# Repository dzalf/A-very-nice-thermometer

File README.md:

# A-very-nice-thermometer
A decorative thermometer based on the LM95071

Result from my first explorations with KiCAD 5 back in 2018 (?). Recently upgraded to KiCAD 7.0 and ported to Cadlab.io

Tons of corrections are still pending, however, the original design remains intact.

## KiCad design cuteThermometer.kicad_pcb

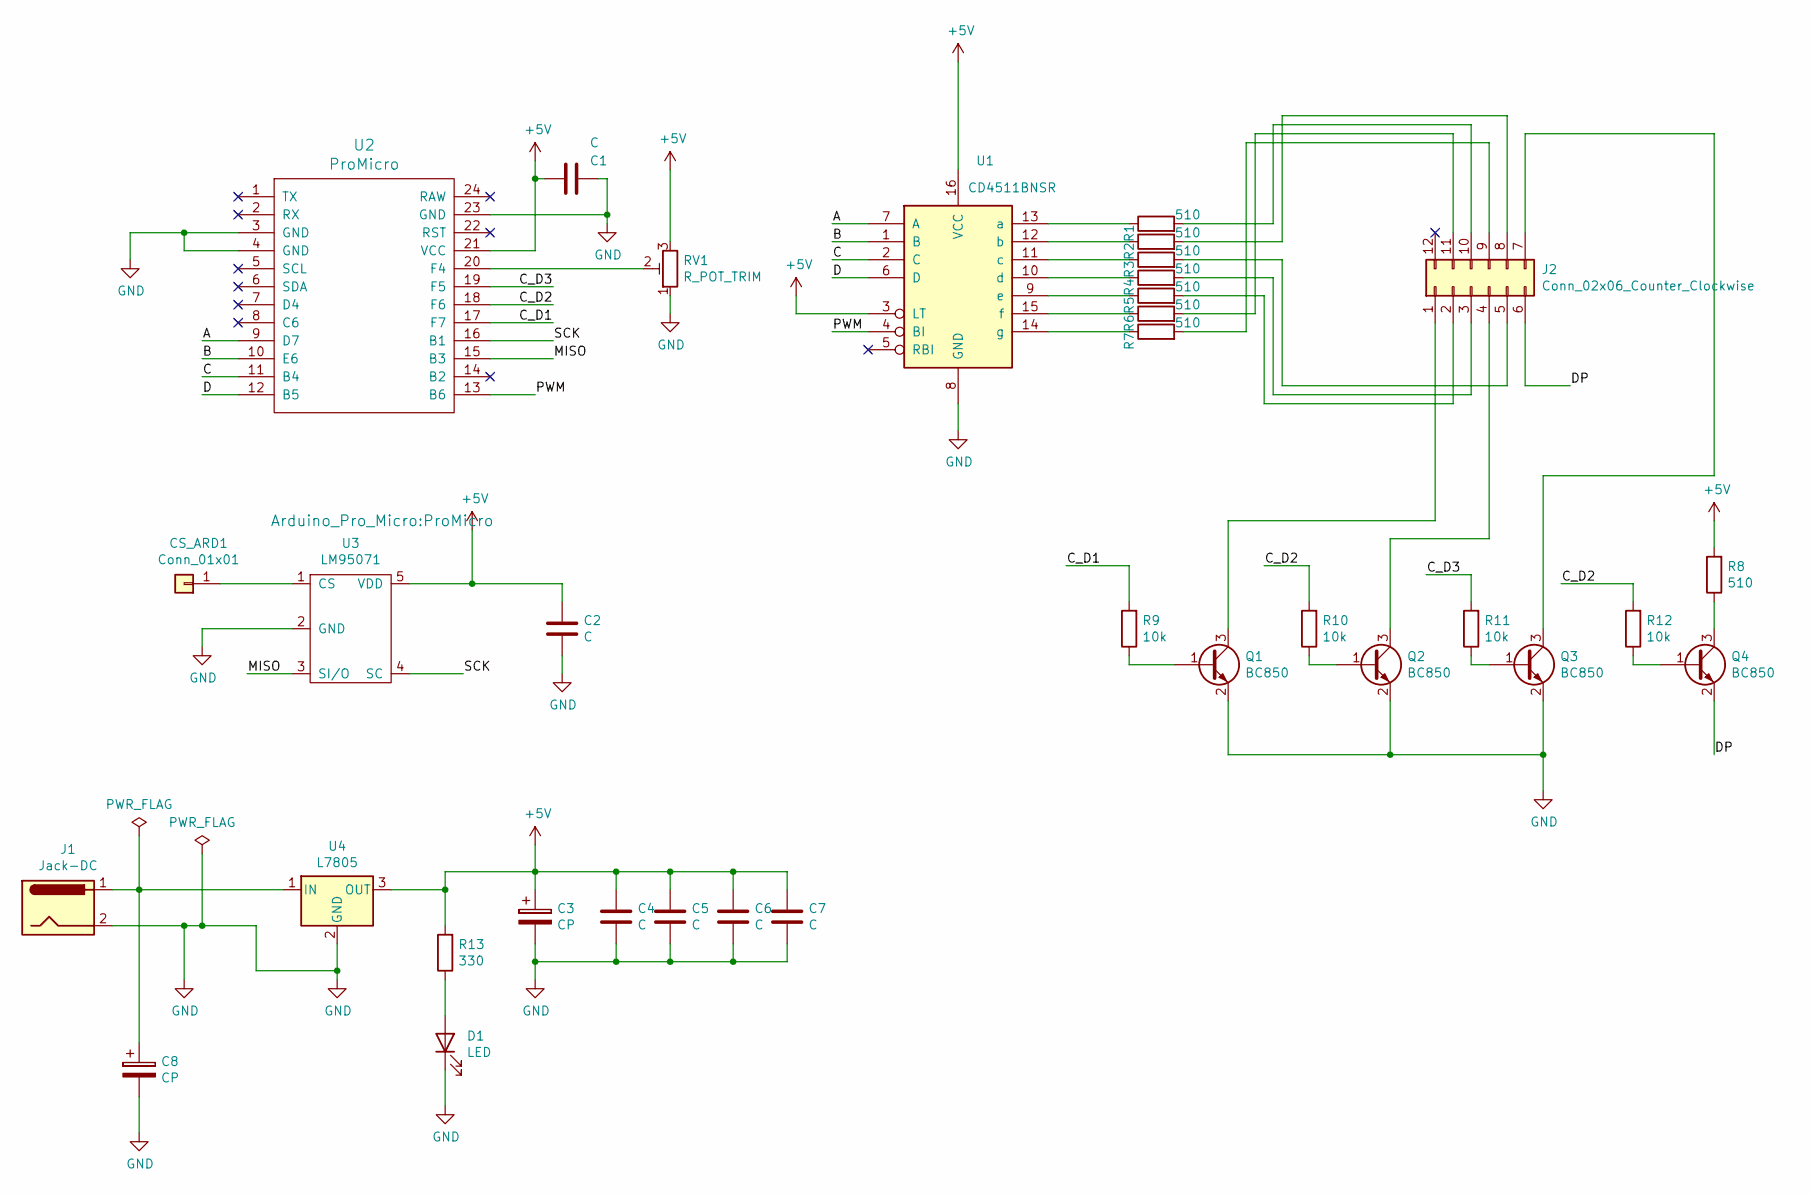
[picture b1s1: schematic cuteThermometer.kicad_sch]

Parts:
C1, C2, C4, C5, C6, C7: C; C_0805_2012Metric_Pad1.15x1.40mm_HandSolder
C3, C8: CP; CP_Elec_4x5.4
CS_ARD1: Conn_01x01; PinHeader_1x01_P1.00mm_Vertical
D1: LED; LED_1206_3216Metric_Pad1.42x1.75mm_HandSolder
J1: Jack-DC; BarrelJack_Wuerth_6941xx301002
J2: Conn_02x06_Counter_Clockwise; PinHeader_2x06_P2.54mm_Vertical
Q1, Q2, Q3, Q4: BC850; SOT-23
R1, R2, R3, R4, R5, R6, R7, R8: 510; R_0805_2012Metric_Pad1.15x1.40mm_HandSolder
R9, R10, R11, R12: 10k; R_0805_2012Metric_Pad1.15x1.40mm_HandSolder
R13: 330; R_0805_2012Metric_Pad1.15x1.40mm_HandSolder
RV1: R_POT_TRIM; Potentiometer_Trimmer-EVM3E
U1: CD4511BNSR; SOP-16_4.4x10.4mm_P1.27mm
U2: ProMicro
U3: LM95071; SOT-23-5_HandSoldering
U4: L7805; TO-252-3_TabPin2

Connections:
+5V: C1.2, C2.1, C3.1, C4.1, C5.1, C6.1, C7.1, R8.2, R13.2, RV1.3, U1.3 (LT), U1.16 (VCC), U2.21 (VCC), U3.5 (VDD), U4.3 (OUT)
/A: U1.7 (A), U2.9 (D7)
/B: U1.1 (B), U2.10 (E6)
/C: U1.2 (C), U2.11 (B4)
/C_D1: R9.2, U2.17 (F7)
/C_D2: R10.2, R12.2, U2.18 (F6)
/C_D3: R11.2, U2.19 (F5)
/D: U1.6 (D), U2.12 (B5)
/DP: J2.6, Q4.2 (E)
/MISO: U2.15 (B3), U3.3 (SI/O)
/PWM: U1.4 (BI), U2.13 (B6)
/SCK: U2.16 (B1), U3.4 (SC)
GND: C1.1, C2.2, C3.2, C4.2, C5.2, C6.2, C7.2, C8.2, D1.1 (K), J1.2, Q1.2 (E), Q2.2 (E), Q3.2 (E), RV1.1, U1.8 (GND), U2.3 (GND), U2.4 (GND), U2.23 (GND), U3.2 (GND), U4.2 (GND)
unnamed: C8.1, J1.1, U4.1 (IN)
unnamed: CS_ARD1.1, U3.1 (CS)
unnamed: D1.2 (A), R13.1
unnamed: J2.1, Q1.3 (C)
unnamed: J2.2, R5.2
unnamed: J2.3, R4.2
unnamed: J2.4, Q2.3 (C)
unnamed: J2.5, R3.2
unnamed: J2.7, Q3.3 (C)
unnamed: J2.8, R2.2
unnamed: J2.9, R7.2
unnamed: J2.10, R1.2
unnamed: J2.11, R6.2
unnamed: Q1.1 (B), R9.1
unnamed: Q2.1 (B), R10.1
unnamed: Q3.1 (B), R11.1
unnamed: Q4.1 (B), R12.1
unnamed: Q4.3 (C), R8.1
unnamed: R1.1, U1.13 (a)
unnamed: R2.1, U1.12 (b)
unnamed: R3.1, U1.11 (c)
unnamed: R4.1, U1.10 (d)
unnamed: R5.1, U1.9 (e)
unnamed: R6.1, U1.15 (f)
unnamed: R7.1, U1.14 (g)
unnamed: RV1.2, U2.20 (F4)

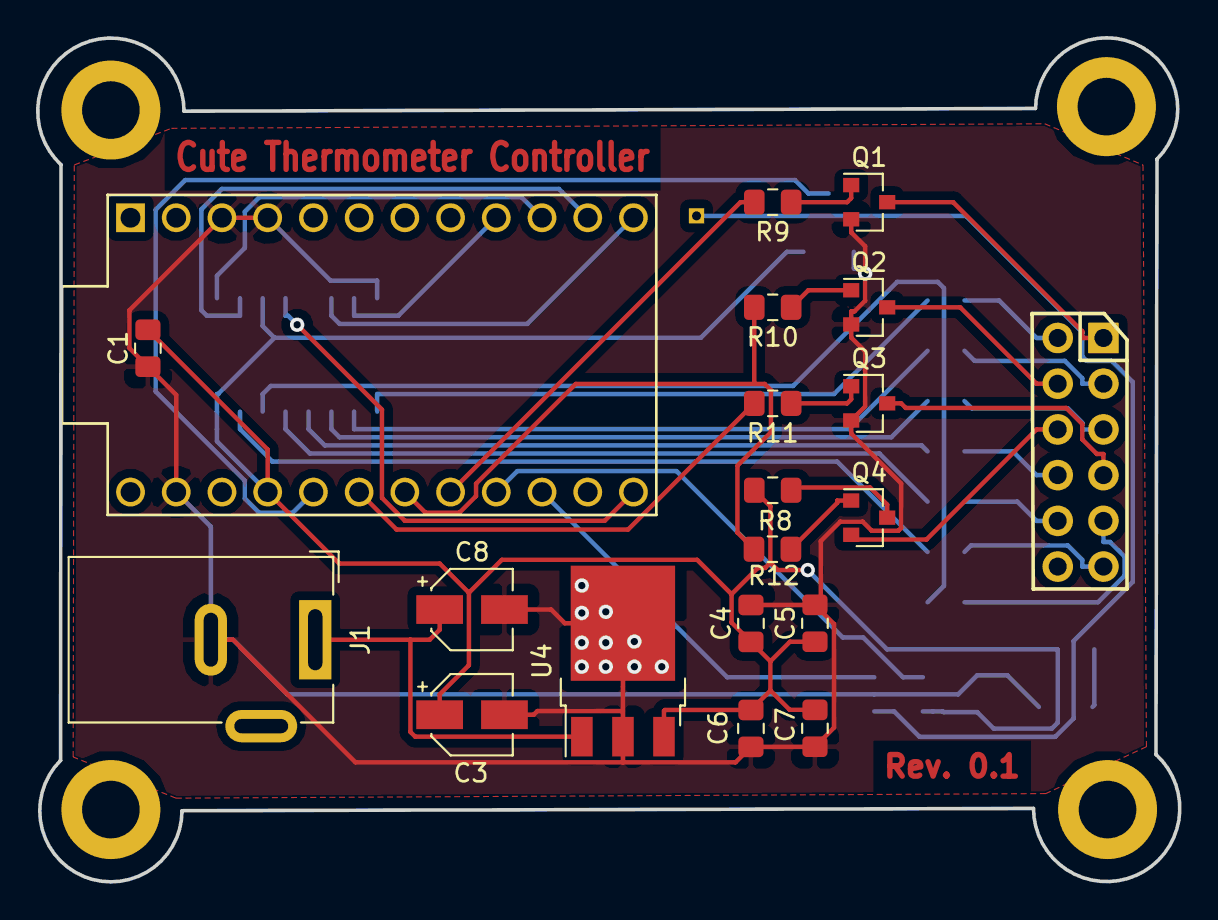
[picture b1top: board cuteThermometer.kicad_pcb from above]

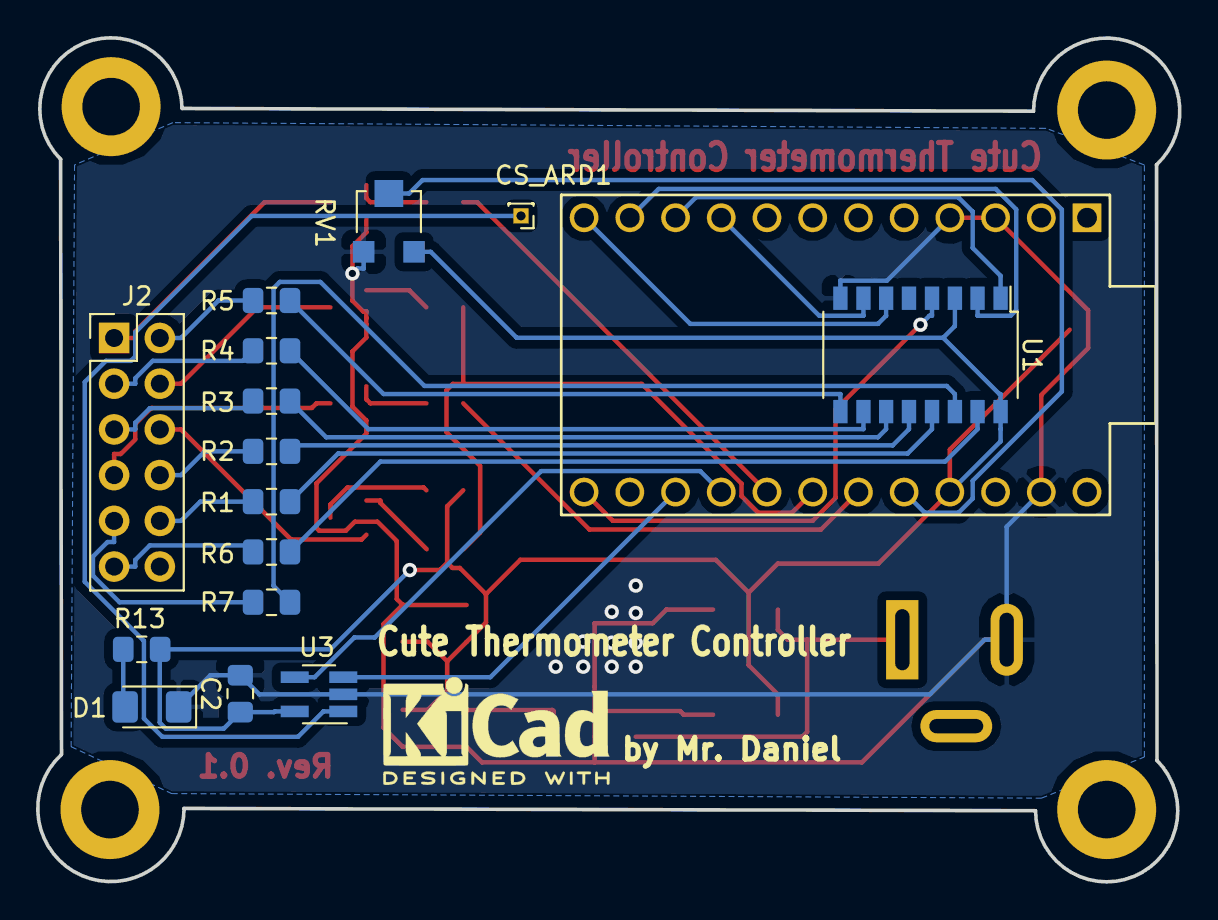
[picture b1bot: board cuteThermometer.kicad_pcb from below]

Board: 2 copper layers, 63.4 x 46.9 mm, 38 parts (16 on the bottom side), 39 nets.

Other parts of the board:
M1, M2, M3, M4: MountingHole_3.2mm_M3_ISO14580_Pad

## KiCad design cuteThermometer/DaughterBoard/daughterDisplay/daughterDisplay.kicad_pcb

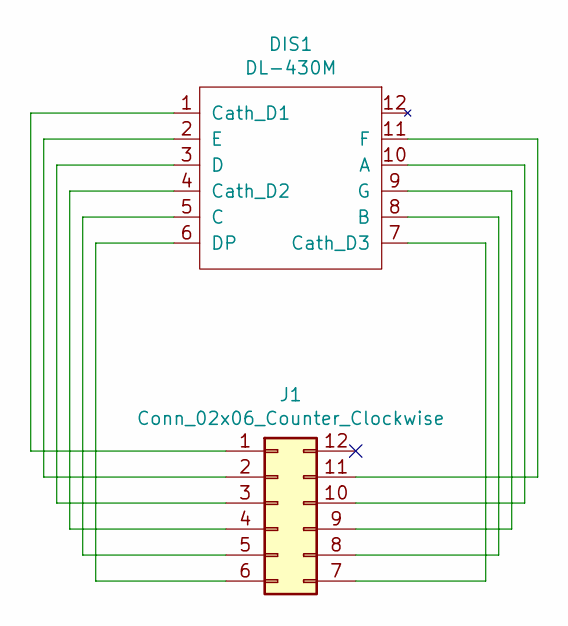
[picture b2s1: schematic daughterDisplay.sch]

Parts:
DIS1: DL-430M; DIP-12_W7.62mm_Socket_LongPads
J1: Conn_02x06_Counter_Clockwise; PinHeader_2x06_P2.54mm_Vertical

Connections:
unnamed: DIS1.1 (Cath_D1), J1.1
unnamed: DIS1.2 (E), J1.2
unnamed: DIS1.3 (D), J1.3
unnamed: DIS1.4 (Cath_D2), J1.4
unnamed: DIS1.5 (C), J1.5
unnamed: DIS1.6 (DP), J1.6
unnamed: DIS1.7 (Cath_D3), J1.7
unnamed: DIS1.8 (B), J1.8
unnamed: DIS1.9 (G), J1.9
unnamed: DIS1.10 (A), J1.10
unnamed: DIS1.11 (F), J1.11

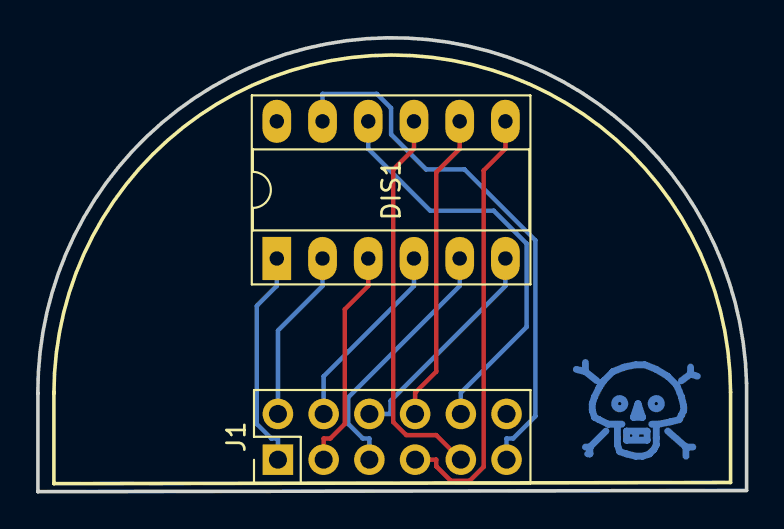
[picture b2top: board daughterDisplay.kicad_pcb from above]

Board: 2 copper layers, 39.4 x 25.2 mm, 3 parts (1 on the bottom side), 11 nets.

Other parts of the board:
by Mr. Dano: Symbol_Danger_CopperTop_Small

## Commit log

2019-02-19 Add files via upload
    This folder contains the two main PCB designs for the processing board and the daughter display board
2019-02-19 Add files via upload
    Arduino code for the thermometer
2019-02-19 Create Issues.md
    A summary of issues that will help to improve the design and performance of this little dude
2019-02-19 Update firmware.ino
    Commented the code and corrected variable declaration issues
2023-03-12 Added project from updated KiCAD 7 version
2023-03-12 Rearranged files. Upgraded the project to KiCAD 7
2023-03-13 Reduced pictures file size since they were huge and looked bad in the browser
